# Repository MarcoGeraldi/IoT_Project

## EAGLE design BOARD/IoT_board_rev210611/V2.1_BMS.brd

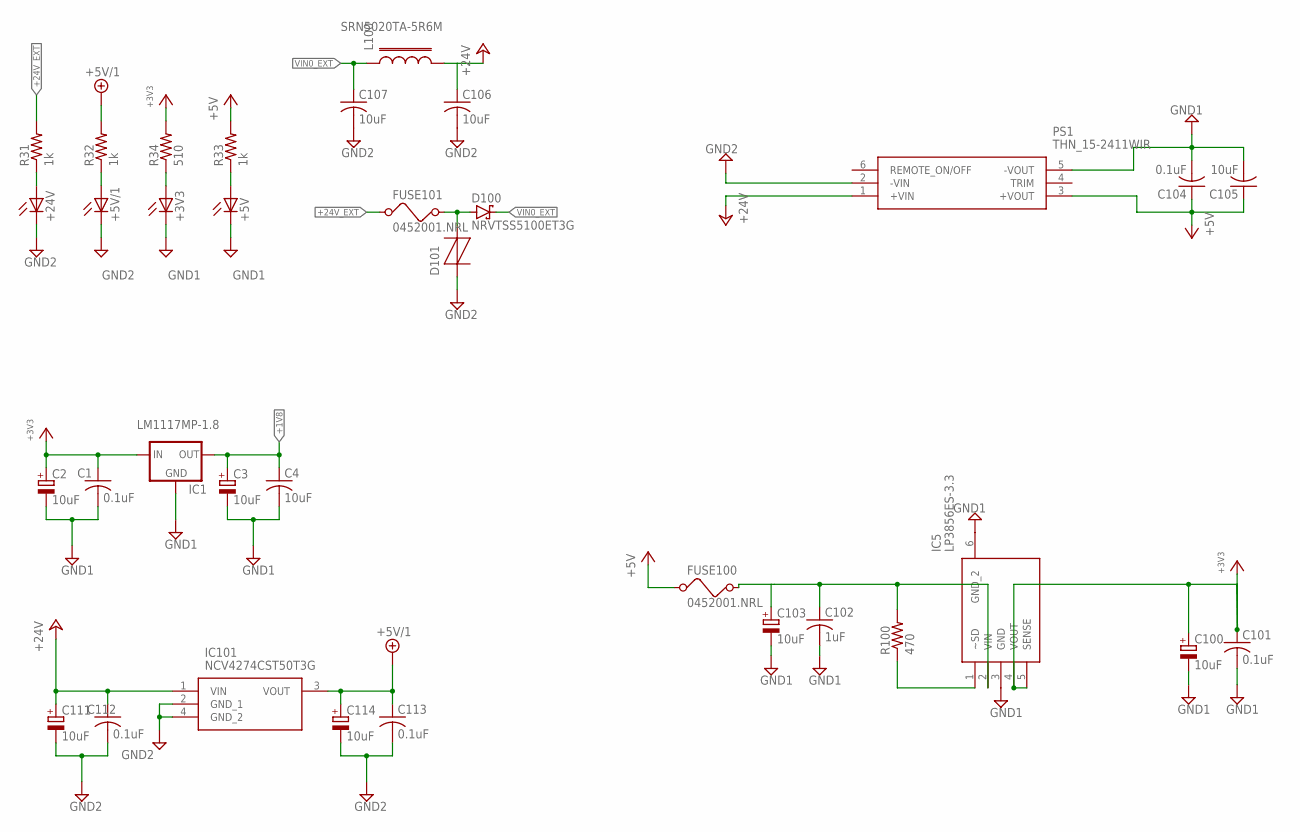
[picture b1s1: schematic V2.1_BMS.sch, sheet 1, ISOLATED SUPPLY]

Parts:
+3V3, +5V, +5V/1, +24V: LED0603; LED-0603
C1, C101, C104, C112, C113: 0.1uF; 0603_INCH:1
C2, C3, C100, C103, C111, C114: 10uF; CAPMP3528X210N
C4, C105, C106, C107: 10uF; 0603_INCH:1
C102: 1uF; 0603_INCH:1
D100: NRVTSS5100ET3G; LIBRARY_DIODES_FUSE_SMB-2
D101: P0300SCLRP; LIBRARY_DIODES_FUSE_SMB
FUSE100, FUSE101: 0452001.NRL; LIBRARY_DIODES_FUSE_452_454
IC1: LM1117MP-1.8; SOT223:1
IC5: LP3856ES-3.3; TO170P1435X465-6N
IC101: NCV4274CST50T3G; SOT223
L100: SRN5020TA-5R6M; LIBRARY_DIODES_FUSE_L_5X5
PS1: THN_15-2411WIR; THN152415WIR
R31, R32, R33: 1k; 0603_INCH
R34: 510; 0603_INCH
R100: 470; 0603_INCH

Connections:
+1V8: C3.1 (+), C4.1, IC1.2 (OUT), IC1.4 (OUT); also elsewhere on the board
+3V3: C1.1, C2.1 (+), C100.1 (+), C101.1, IC1.3 (IN), IC5.4 (VOUT), IC5.5 (SENSE), R34.2; also elsewhere on the board
+5V: C104.1, C105.1, FUSE100.P$1 (1), PS1.3 (+VOUT), R33.2; also elsewhere on the board
+5V/1: C113.1, C114.1 (+), IC101.3 (VOUT), R32.2; also elsewhere on the board
+24V: C106.1, C111.1 (+), C112.1, IC101.1 (VIN), L100.P$2 (2), PS1.1 (+VIN)
+24V_EXT: FUSE101.P$1 (1), R31.2; also elsewhere on the board
GND1: +3V3.C, +5V.C, C1.2, C2.2 (-), C3.2 (-), C4.2, C100.2 (-), C101.2, C102.2, C103.2 (-), C104.2, C105.2, IC1.1 (GND), IC5.3 (GND), IC5.6 (GND_2), PS1.5 (-VOUT); also elsewhere on the board
GND2: +5V/1.C, +24V.C, C106.2, C107.2, C111.2 (-), C112.2, C113.2, C114.2 (-), D101.2 (T), IC101.2 (GND_1), IC101.4 (GND_2), PS1.2 (-VIN); also elsewhere on the board
unnamed: C102.1, C103.1 (+), FUSE100.P$2 (2), IC5.2 (VIN), R100.2
unnamed: D100.A, D101.1 (R), FUSE101.P$2 (2)
unnamed: IC5.1 (~SD), R100.1
unnamed: +5V/1.A, R32.1
unnamed: +5V.A, R33.1
unnamed: +24V.A, R31.1
unnamed: +3V3.A, R34.1
VIN0_EXT: C107.1, D100.C, L100.P$1 (1)

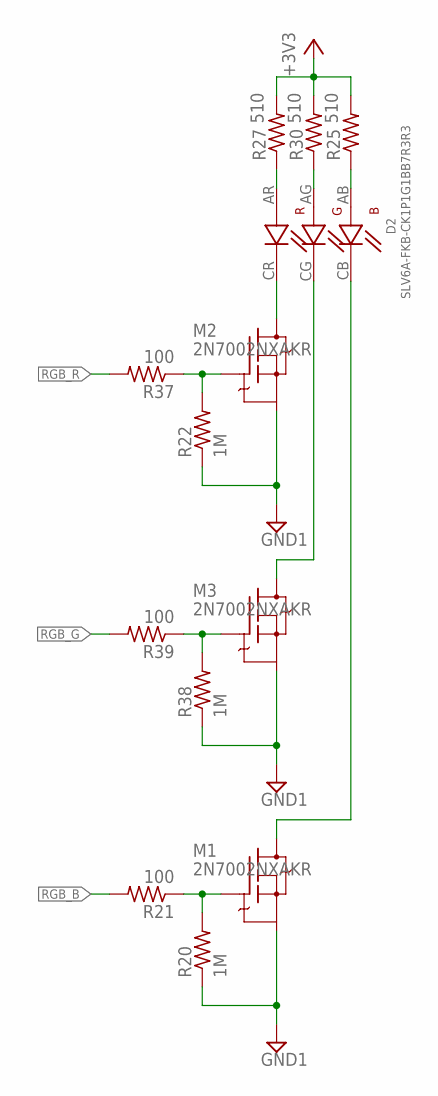
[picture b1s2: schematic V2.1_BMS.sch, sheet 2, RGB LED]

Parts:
D2: SLV6A-FKB-CK1P1G1BB7R3R3; PLCC-6-LED_PLCC-6-LED
M1, M2, M3: 2N7002NXAKR; BEOND_SOT23
R20, R22, R38: 1M; 0603_INCH
R21, R37, R39: 100; 0603_INCH
R25, R27, R30: 510; 0603_INCH

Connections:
+3V3: R25.2, R27.2, R30.2; also elsewhere on the board
GND1: M1.2 (S), M2.2 (S), M3.2 (S), R20.1, R22.1, R38.1; also elsewhere on the board
unnamed: D2.AR (RA), R27.1
unnamed: D2.AG (GA), R30.1
unnamed: D2.AB (BA), R25.1
unnamed: M3.1 (G), R38.2, R39.1
unnamed: D2.CG (GC), M3.3 (D)
unnamed: M1.1 (G), R20.2, R21.1
unnamed: D2.CB (BC), M1.3 (D)
unnamed: M2.1 (G), R22.2, R37.1
unnamed: D2.CR (RC), M2.3 (D)
RGB_B: R21.2; also elsewhere on the board
RGB_G: R39.2; also elsewhere on the board
RGB_R: R37.2; also elsewhere on the board

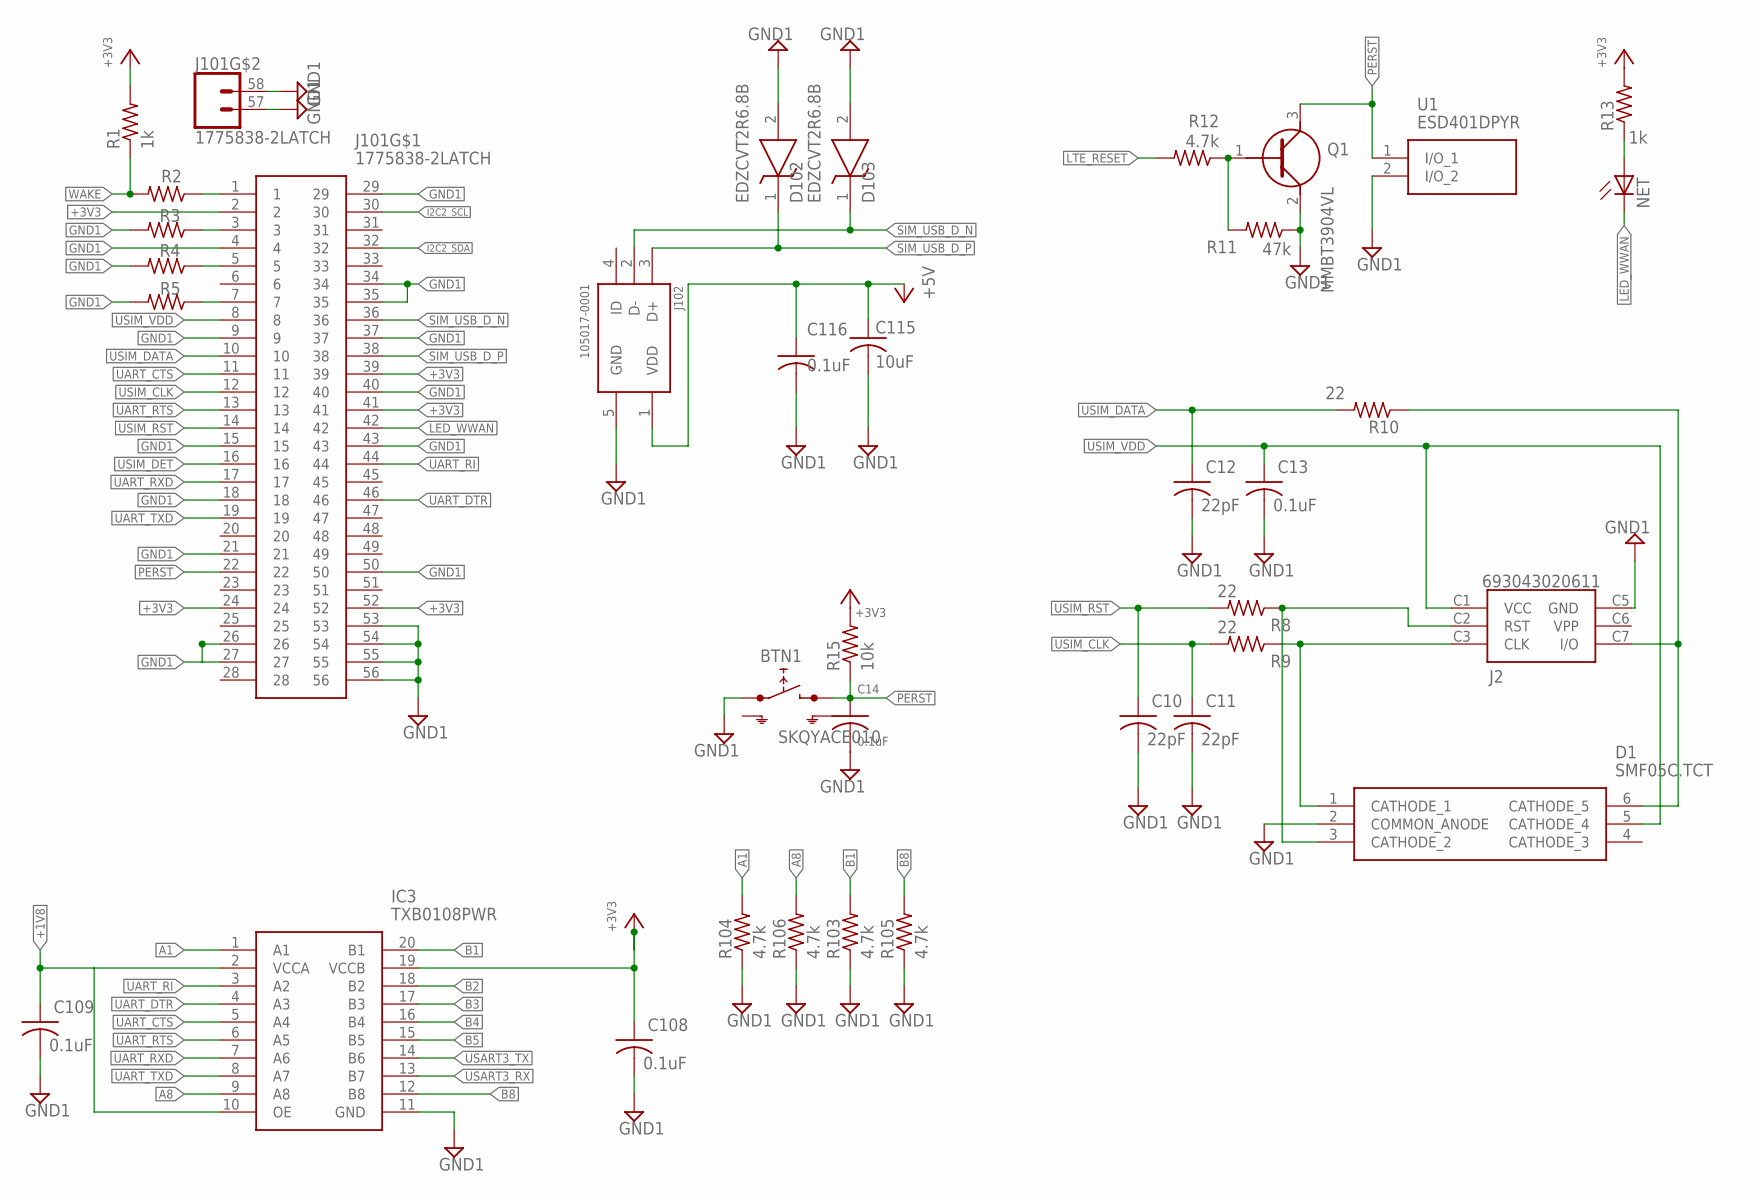
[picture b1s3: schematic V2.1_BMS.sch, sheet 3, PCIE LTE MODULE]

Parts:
BTN1: SKQYACE010; BOTON_LED_SKQYACE010
C10, C11, C12: 22pF; 0603_INCH:1
C13, C14, C108, C109, C116: 0.1uF; 0603_INCH:1
C115: 10uF; 0603_INCH:1
D1: SMF05C.TCT; SOT65P210X110-6N
D102, D103: EDZCVT2R6.8B; SODFL1608X70N
IC3: TXB0108PWR; SOP65P640X120-20N
J2: 693043020611
J101: 1775838-2LATCH; 17758382_LATCH
J102: 105017-0001; MOLEX_105017-0001
NET: LED0603; LED-0603
Q1: MMBT3904VL; SOT95P230X110-3N
R1, R13: 1k; 0603_INCH
R2, R3, R4, R5: 0; 0603_INCH
R8, R9, R10: 22; 0603_INCH
R11: 47k; 0603_INCH
R12, R103, R104, R105, R106: 4.7k; 0603_INCH
R15: 10k; 0603_INCH
U1: ESD401DPYR

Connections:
+1V8: C109.1, IC3.2 (VCCA), IC3.10 (OE); also elsewhere on the board
+3V3: C108.1, IC3.19 (VCCB), J101.2, J101.24, J101.39, J101.41, J101.52, R1.2, R13.2, R15.2; also elsewhere on the board
+5V: C115.1, C116.1, J102.1 (VDD); also elsewhere on the board
A1: IC3.1 (A1), R104.2
A8: IC3.9 (A8), R106.2
B1: IC3.20 (B1), R103.2
B2: IC3.18 (B2)
B3: IC3.17 (B3)
B4: IC3.16 (B4)
B5: IC3.15 (B5)
B8: IC3.12 (B8), R105.2
GND1: BTN1.1 (1.1), C10.2, C11.2, C12.2, C13.2, C14.2, C108.2, C109.2, C115.2, C116.2, D1.2 (COMMON_ANODE), D102.2 (A), D103.2 (A), IC3.11 (GND), J2.C5 (GND), J101.4, J101.9, J101.15, J101.18, J101.21, J101.26, J101.27, J101.29, J101.34, J101.35, J101.37, J101.40, J101.43, J101.50, J101.53, J101.54, J101.55, J101.56, J101.57 (1), J101.58 (2), J102.5 (GND), Q1.2 (E), R3.2, R4.2, R5.2, R11.1, R103.1, R104.1, R105.1, R106.1, U1.2 (I/O_2); also elsewhere on the board
I2C2_SCL: J101.30; also elsewhere on the board
I2C2_SDA: J101.32; also elsewhere on the board
LED_WWAN: J101.42, NET.C
LTE_RESET: R12.2
unnamed: J101.3, R3.1
unnamed: J101.5, R4.1
unnamed: Q1.1 (B), R11.2, R12.1
unnamed: NET.A, R13.1
unnamed: D1.3 (CATHODE_2), J2.C2 (RST), R8.1
unnamed: J101.7, R5.1
unnamed: J101.1, R2.1
PERST: BTN1.2 (2.1), C14.1, J101.22, Q1.3 (C), R15.1, U1.1 (I/O_1)
SIM_USB_D_N: D103.1 (K), J101.36, J102.2 (D-)
SIM_USB_D_P: D102.1 (K), J101.38, J102.3 (D+)
UART_CTS: IC3.5 (A4), J101.11
UART_DTR: IC3.4 (A3), J101.46
UART_RI: IC3.3 (A2), J101.44
UART_RTS: IC3.6 (A5), J101.13
UART_RXD: IC3.7 (A6), J101.17
UART_TXD: IC3.8 (A7), J101.19
USART3_RX: IC3.13 (B7); also elsewhere on the board
USART3_TX: IC3.14 (B6); also elsewhere on the board
USIM_CLK: C11.1, J101.12, R9.2
USIM_DATA: C12.1, J101.10, R10.2
USIM_DET: J101.16
USIM_RST: C10.1, J101.14, R8.2
USIM_VDD: C13.1, D1.5 (CATHODE_4), J2.C1 (VCC), J101.8
WAKE: R1.1, R2.2
_USIM_CLK: D1.1 (CATHODE_1), J2.C3 (CLK), R9.1
_USIM_DATA: D1.6 (CATHODE_5), J2.C7 (I/O), R10.1

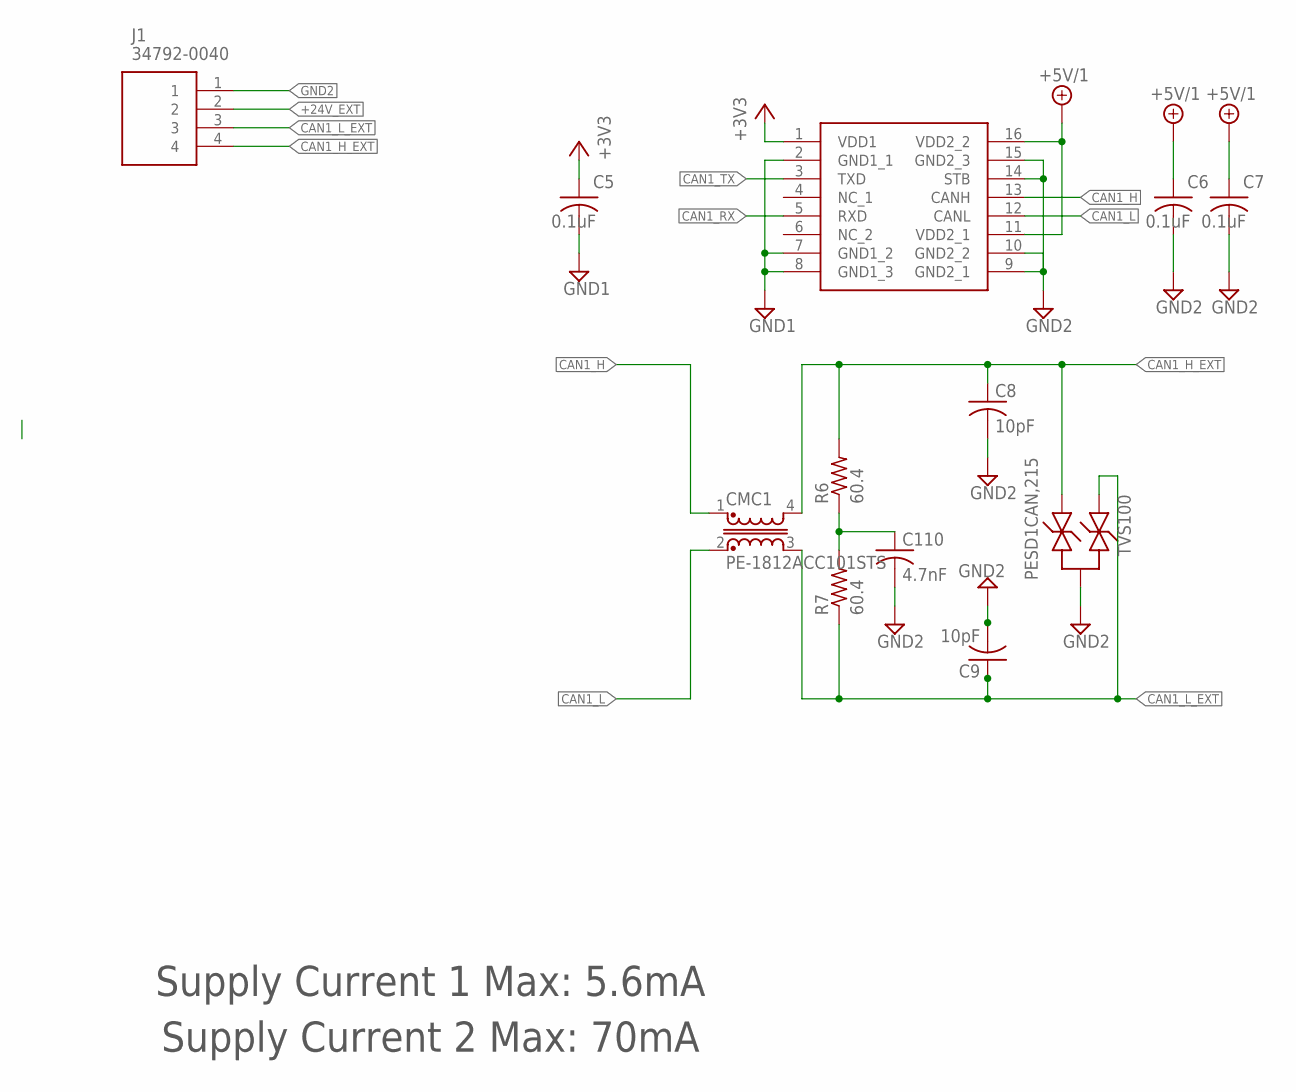
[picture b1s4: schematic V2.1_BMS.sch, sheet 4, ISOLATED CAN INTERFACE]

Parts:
C5, C6, C7: 0.1uF; 0603_INCH:1
C8, C9: 10pF; 0603_INCH:1
C110: 4.7nF; 0603_INCH:1
CMC1: PE-1812ACC101STS; BEOND_L_1812ACC
IC2: TJA1052IT/2Y; TJA1052IT_2Y_SOIC127P1032X265-16N
J1: 34792-0040; 347920040
R6, R7: 60.4; 0603_INCH
TVS100: PESD1CAN,215; BEOND_SOT23

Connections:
+3V3: C5.1, IC2.1 (VDD1); also elsewhere on the board
+5V/1: C6.1, C7.1, IC2.11 (VDD2_1), IC2.16 (VDD2_2); also elsewhere on the board
+24V_EXT: J1.2; also elsewhere on the board
CAN1_H: CMC1.1, IC2.13 (CANH)
CAN1_H_EXT: C8.1, CMC1.4, J1.4, R6.2, TVS100.2
CAN1_L: CMC1.2, IC2.12 (CANL)
CAN1_L_EXT: C9.1, CMC1.3, J1.3, R7.1, TVS100.1
CAN1_RX: IC2.5 (RXD); also elsewhere on the board
CAN1_TX: IC2.3 (TXD); also elsewhere on the board
GND1: C5.2, IC2.2 (GND1_1), IC2.7 (GND1_2), IC2.8 (GND1_3); also elsewhere on the board
GND2: C6.2, C7.2, C8.2, C9.2, C110.2, IC2.9 (GND2_1), IC2.10 (GND2_2), IC2.14 (STB), IC2.15 (GND2_3), J1.1, TVS100.3; also elsewhere on the board
unnamed: C110.1, R6.1, R7.2

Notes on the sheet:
Supply Current 2 Max: 70mA
Supply Current 1 Max: 5.6mA

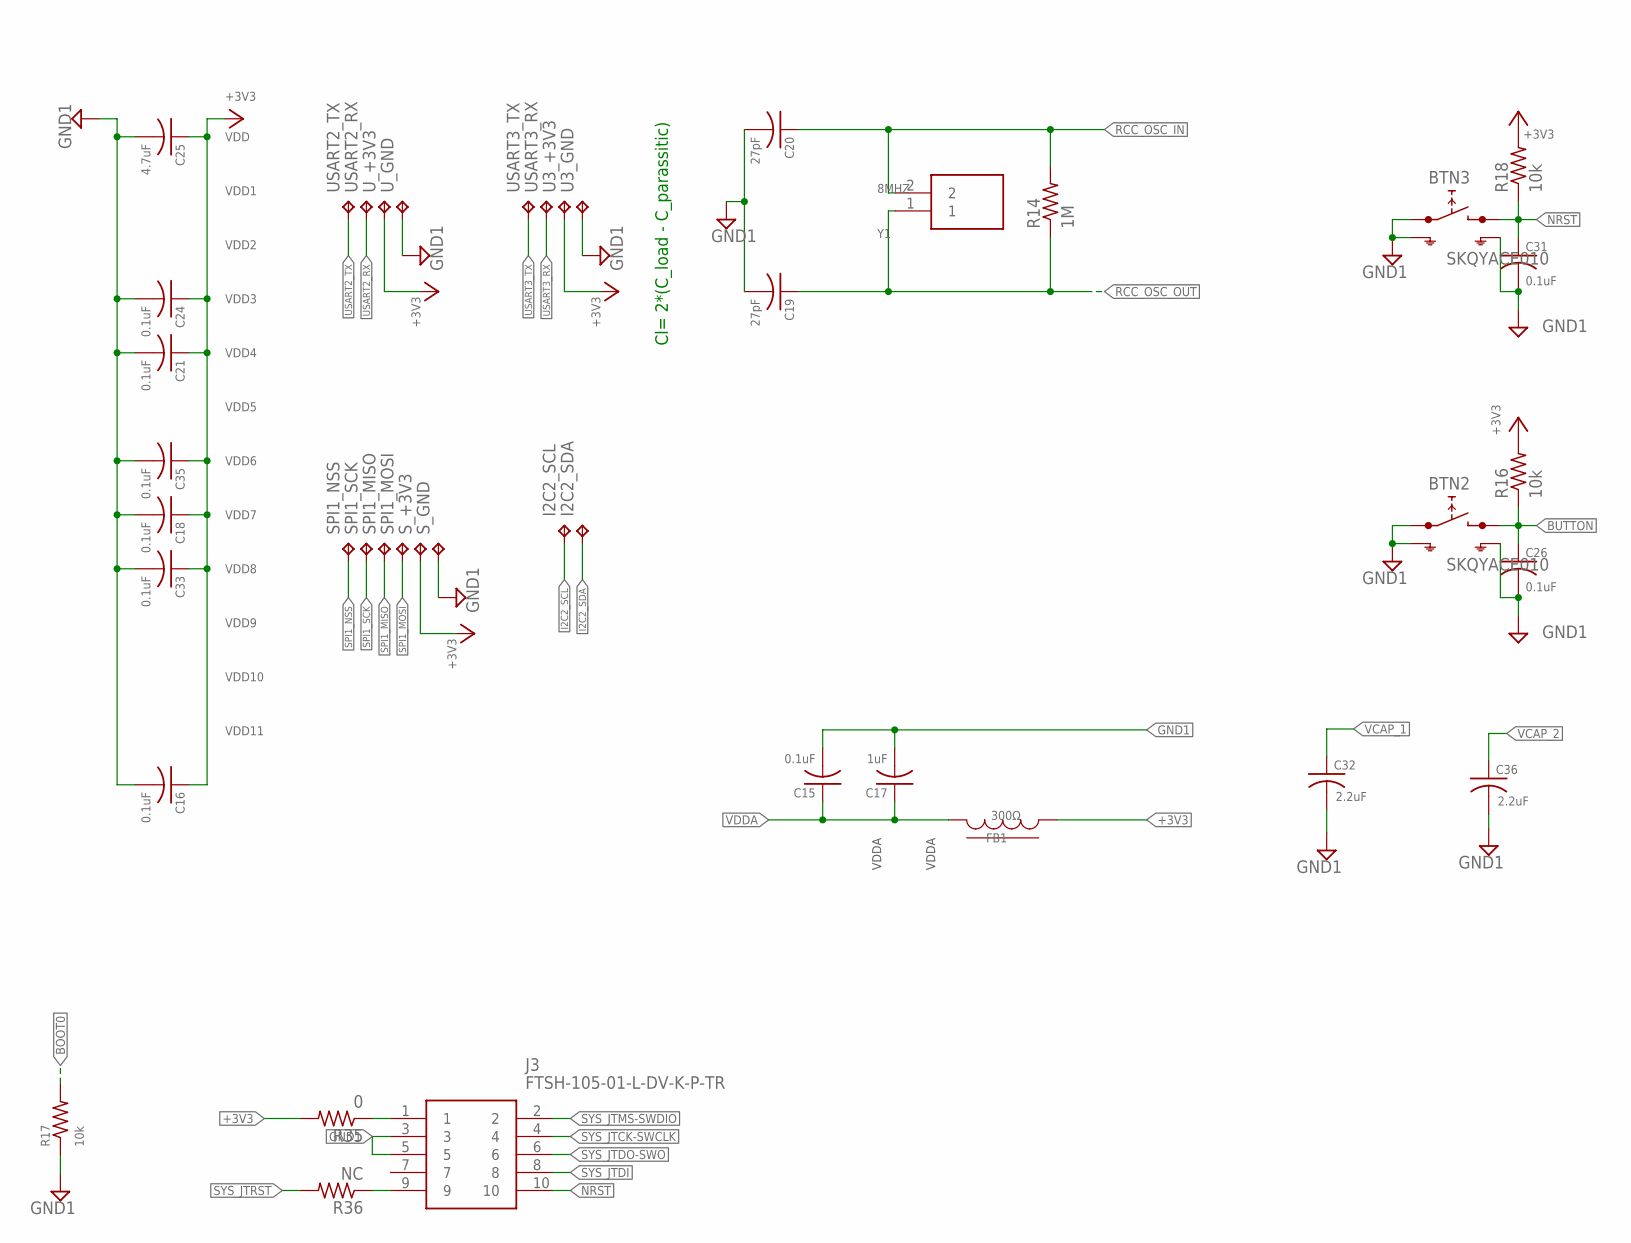
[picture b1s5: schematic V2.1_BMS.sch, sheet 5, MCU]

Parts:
BTN2, BTN3: SKQYACE010; BOTON_LED_SKQYACE010
C15, C16, C18, C21, C24, C33, C35: 0.1uF; 0603_INCH:1
C17: 1uF; 0603_INCH:1
C19, C20: 27pF; 0603_INCH
C25: 4.7uF; 0603_INCH:1
C26, C31: 0.1uF; 0603_INCH
C32, C36: 2.2uF; 0603_INCH:1
FB1: 300Ω; 0603_INCH
I2C2_SCL, I2C2_SDA: TPTP09R; TP09R
J3: FTSH-105-01-L-DV-K-P-TR; FTSH10501LDVKPTR
R14: 1M; 0603_INCH
R16, R17, R18: 10k; 0603_INCH
R35: 0; 0603_INCH
R36: NC; 0603_INCH
SPI1_MISO, SPI1_MOSI, SPI1_NSS, SPI1_SCK: TPTP09R; TP09R
S_+3V3: TPTP09R; TP09R
S_GND: TPTP09SQ; TP09SQ
U3_+3V3: TPTP09R; TP09R
U3_GND: TPTP09SQ; TP09SQ
USART2_RX, USART2_TX, USART3_RX, USART3_TX: TPTP09R; TP09R
U_+3V3: TPTP09R; TP09R
U_GND: TPTP09SQ; TP09SQ
Y1: 8MHZ; RESC3226X100N

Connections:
+3V1: U3_+3V3.TP
+3V3: C16.1, C18.1, C21.1, C24.1, C25.1, C33.1, C35.1, FB1.1, R16.2, R18.2, R35.2, S_+3V3.TP, U_+3V3.TP; also elsewhere on the board
BOOT0: R17.2; also elsewhere on the board
BUTTON: BTN2.2 (2.1), C26.1, R16.1; also elsewhere on the board
GND1: BTN2.1 (1.1), BTN2.GND1 (SH), BTN2.GND2 (SH1), BTN3.1 (1.1), BTN3.GND1 (SH), BTN3.GND2 (SH1), C15.2, C16.2, C17.2, C18.2, C19.2, C20.2, C21.2, C24.2, C25.2, C26.2, C31.2, C32.2, C33.2, C35.2, C36.2, J3.3, J3.5, R17.1, S_GND.TP, U_GND.TP; also elsewhere on the board
GND3: U3_GND.TP
I2C2_SCL: I2C2_SCL.TP; also elsewhere on the board
I2C2_SDA: I2C2_SDA.TP; also elsewhere on the board
unnamed: J3.1, R35.1
unnamed: J3.9, R36.1
NRST: BTN3.2 (2.1), C31.1, J3.10, R18.1; also elsewhere on the board
RCC_OSC_IN: C20.1, R14.2, Y1.2; also elsewhere on the board
RCC_OSC_OUT: C19.1, R14.1, Y1.1; also elsewhere on the board
SPI1_MISO: SPI1_MISO.TP; also elsewhere on the board
SPI1_MOSI: SPI1_MOSI.TP; also elsewhere on the board
SPI1_NSS: SPI1_NSS.TP; also elsewhere on the board
SPI1_SCK: SPI1_SCK.TP; also elsewhere on the board
SYS_JTCK-SWCLK: J3.4; also elsewhere on the board
SYS_JTDI: J3.8; also elsewhere on the board
SYS_JTDO-SWO: J3.6; also elsewhere on the board
SYS_JTMS-SWDIO: J3.2; also elsewhere on the board
SYS_JTRST: R36.2; also elsewhere on the board
USART2_RX: USART2_RX.TP; also elsewhere on the board
USART2_TX: USART2_TX.TP; also elsewhere on the board
USART3_RX: USART3_RX.TP; also elsewhere on the board
USART3_TX: USART3_TX.TP; also elsewhere on the board
VCAP_1: C32.1; also elsewhere on the board
VCAP_2: C36.1; also elsewhere on the board
VDDA: C15.1, C17.1, FB1.2; also elsewhere on the board

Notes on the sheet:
VDD1
VDD2
VDD3
VDD4
VDD
VDD5
VDD6
VDD7
VDD8
VDD9
VDD10
VDD11
VDDA
Cl= 2*(C_load - C_parassitic)

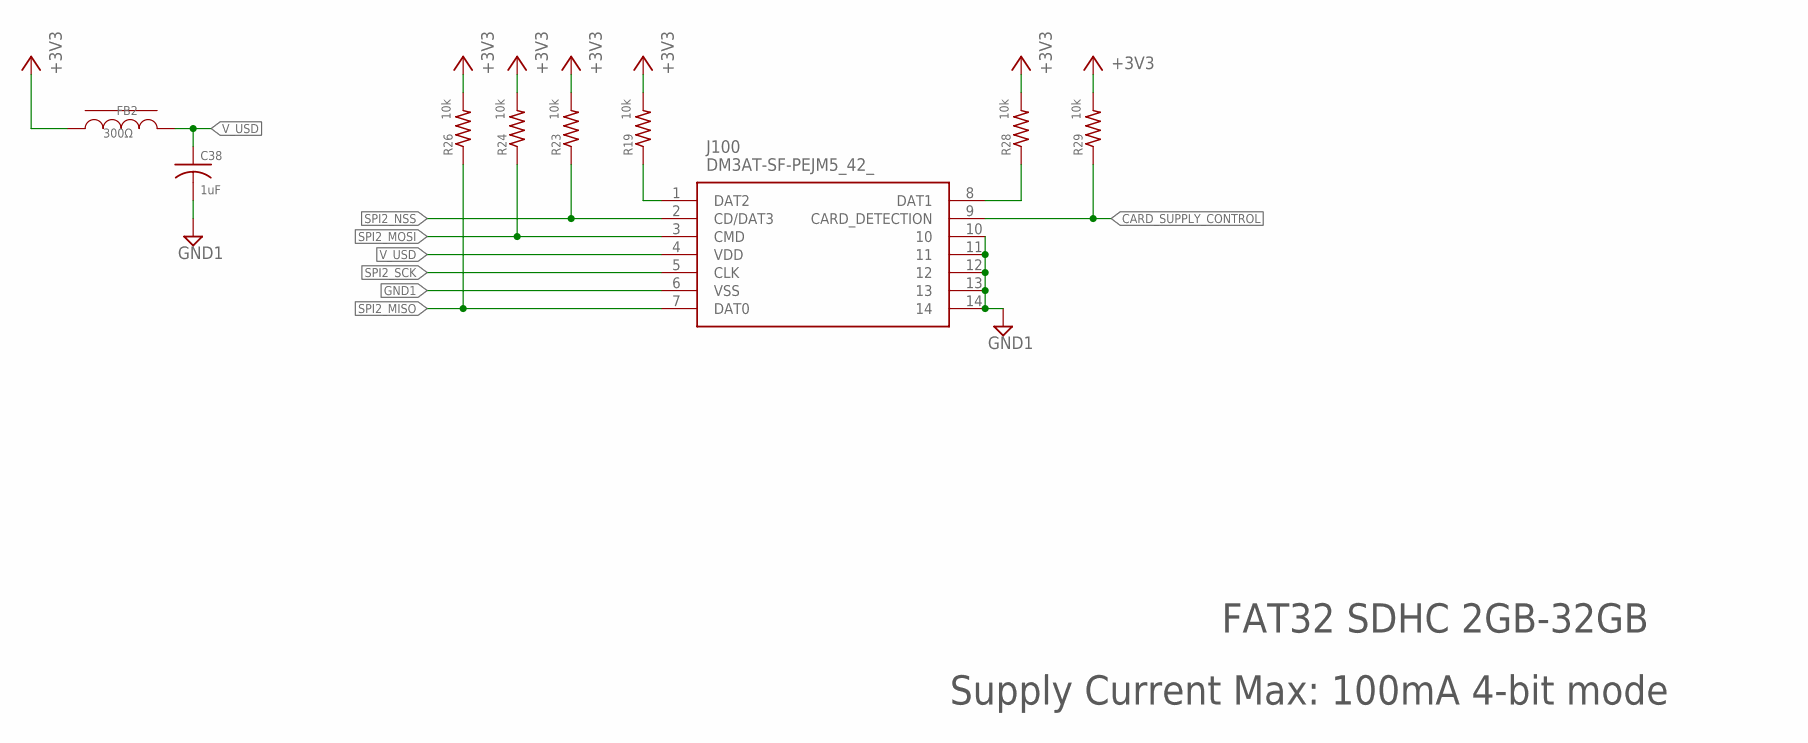
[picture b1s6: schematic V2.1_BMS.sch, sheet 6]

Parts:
C38: 1uF; 0603_INCH
FB2: 300Ω; 0603_INCH
J100: DM3AT-SF-PEJM5_42_; DM3ATSFPEJM542
R19, R23, R24, R26, R28, R29: 10k; 0603_INCH

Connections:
+3V3: FB2.1, R19.2, R23.2, R24.2, R26.2, R28.2, R29.2; also elsewhere on the board
CARD_SUPPLY_CONTROL: J100.9 (CARD_DETECTION), R29.1; also elsewhere on the board
GND1: C38.2, J100.6 (VSS), J100.10, J100.11, J100.12, J100.13, J100.14; also elsewhere on the board
unnamed: J100.1 (DAT2), R19.1
unnamed: J100.8 (DAT1), R28.1
SPI2_MISO: J100.7 (DAT0), R26.1; also elsewhere on the board
SPI2_MOSI: J100.3 (CMD), R24.1; also elsewhere on the board
SPI2_NSS: J100.2 (CD/DAT3), R23.1; also elsewhere on the board
SPI2_SCK: J100.5 (CLK); also elsewhere on the board
V_USD: C38.1, FB2.2, J100.4 (VDD)

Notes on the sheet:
Supply Current Max: 100mA 4-bit mode
FAT32 SDHC 2GB-32GB

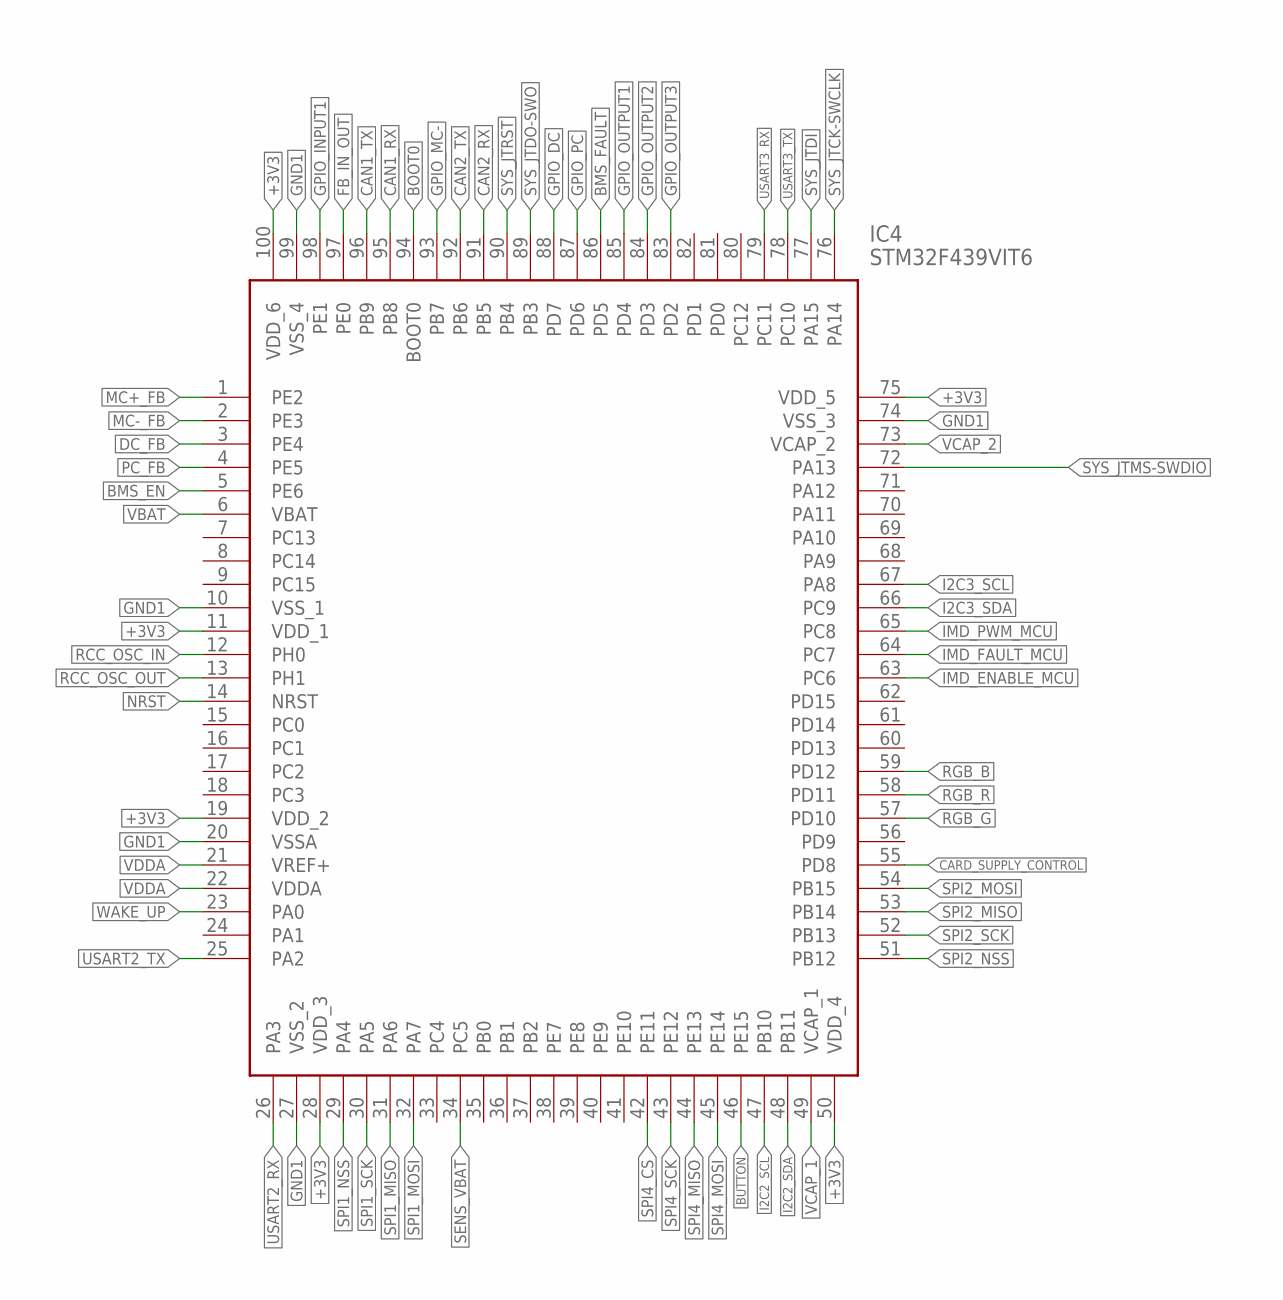
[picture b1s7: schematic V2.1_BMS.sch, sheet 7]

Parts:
IC4: STM32F439VIT6; QFP50P1600X1600X160-100N

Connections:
+3V3: IC4.11 (VDD_1), IC4.19 (VDD_2), IC4.28 (VDD_3), IC4.50 (VDD_4), IC4.75 (VDD_5), IC4.100 (VDD_6); also elsewhere on the board
BMS_EN: IC4.5 (PE6)
BMS_FAULT: IC4.86 (PD5)
BOOT0: IC4.94 (BOOT0); also elsewhere on the board
BUTTON: IC4.46 (PE15); also elsewhere on the board
CAN1_RX: IC4.95 (PB8); also elsewhere on the board
CAN1_TX: IC4.96 (PB9); also elsewhere on the board
CAN2_RX: IC4.91 (PB5)
CAN2_TX: IC4.92 (PB6)
CARD_SUPPLY_CONTROL: IC4.55 (PD8); also elsewhere on the board
DC_FB: IC4.3 (PE4)
FB_IN_OUT: IC4.97 (PE0)
GND1: IC4.10 (VSS_1), IC4.20 (VSSA), IC4.27 (VSS_2), IC4.74 (VSS_3), IC4.99 (VSS_4); also elsewhere on the board
GPIO_DC: IC4.88 (PD7)
GPIO_INPUT1: IC4.98 (PE1)
GPIO_MC-: IC4.93 (PB7)
GPIO_OUTPUT1: IC4.85 (PD4)
GPIO_OUTPUT2: IC4.84 (PD3)
GPIO_OUTPUT3: IC4.83 (PD2)
GPIO_PC: IC4.87 (PD6)
I2C2_SCL: IC4.47 (PB10); also elsewhere on the board
I2C2_SDA: IC4.48 (PB11); also elsewhere on the board
I2C3_SCL: IC4.67 (PA8)
I2C3_SDA: IC4.66 (PC9)
IMD_ENABLE_MCU: IC4.63 (PC6)
IMD_FAULT_MCU: IC4.64 (PC7)
IMD_PWM_MCU: IC4.65 (PC8)
MC+_FB: IC4.1 (PE2)
MC-_FB: IC4.2 (PE3)
NRST: IC4.14 (NRST); also elsewhere on the board
PC_FB: IC4.4 (PE5)
RCC_OSC_IN: IC4.12 (PH0); also elsewhere on the board
RCC_OSC_OUT: IC4.13 (PH1); also elsewhere on the board
RGB_B: IC4.59 (PD12); also elsewhere on the board
RGB_G: IC4.57 (PD10); also elsewhere on the board
RGB_R: IC4.58 (PD11); also elsewhere on the board
SENS_VBAT: IC4.34 (PC5)
SPI1_MISO: IC4.31 (PA6); also elsewhere on the board
SPI1_MOSI: IC4.32 (PA7); also elsewhere on the board
SPI1_NSS: IC4.29 (PA4); also elsewhere on the board
SPI1_SCK: IC4.30 (PA5); also elsewhere on the board
SPI2_MISO: IC4.53 (PB14); also elsewhere on the board
SPI2_MOSI: IC4.54 (PB15); also elsewhere on the board
SPI2_NSS: IC4.51 (PB12); also elsewhere on the board
SPI2_SCK: IC4.52 (PB13); also elsewhere on the board
SPI4_CS: IC4.42 (PE11)
SPI4_MISO: IC4.44 (PE13)
SPI4_MOSI: IC4.45 (PE14)
SPI4_SCK: IC4.43 (PE12)
SYS_JTCK-SWCLK: IC4.76 (PA14); also elsewhere on the board
SYS_JTDI: IC4.77 (PA15); also elsewhere on the board
SYS_JTDO-SWO: IC4.89 (PB3); also elsewhere on the board
SYS_JTMS-SWDIO: IC4.72 (PA13); also elsewhere on the board
SYS_JTRST: IC4.90 (PB4); also elsewhere on the board
USART2_RX: IC4.26 (PA3); also elsewhere on the board
USART2_TX: IC4.25 (PA2); also elsewhere on the board
USART3_RX: IC4.79 (PC11); also elsewhere on the board
USART3_TX: IC4.78 (PC10); also elsewhere on the board
VBAT: IC4.6 (VBAT)
VCAP_1: IC4.49 (VCAP_1); also elsewhere on the board
VCAP_2: IC4.73 (VCAP_2); also elsewhere on the board
VDDA: IC4.21 (VREF+), IC4.22 (VDDA); also elsewhere on the board
WAKE_UP: IC4.23 (PA0)

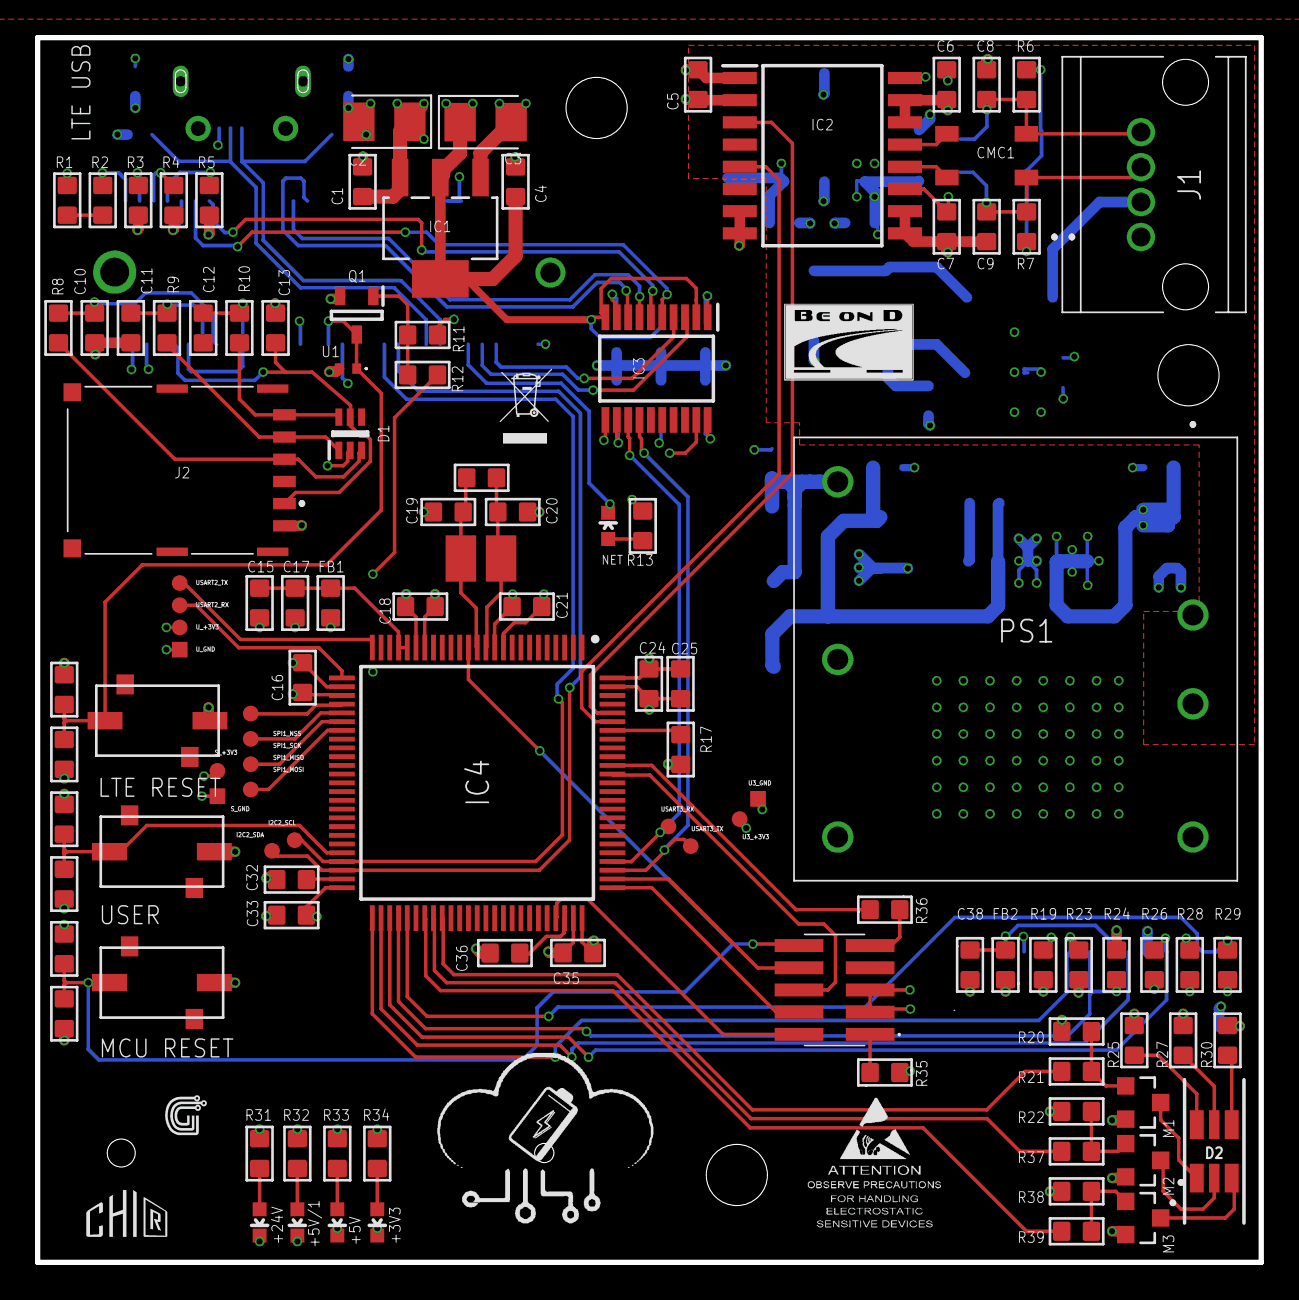
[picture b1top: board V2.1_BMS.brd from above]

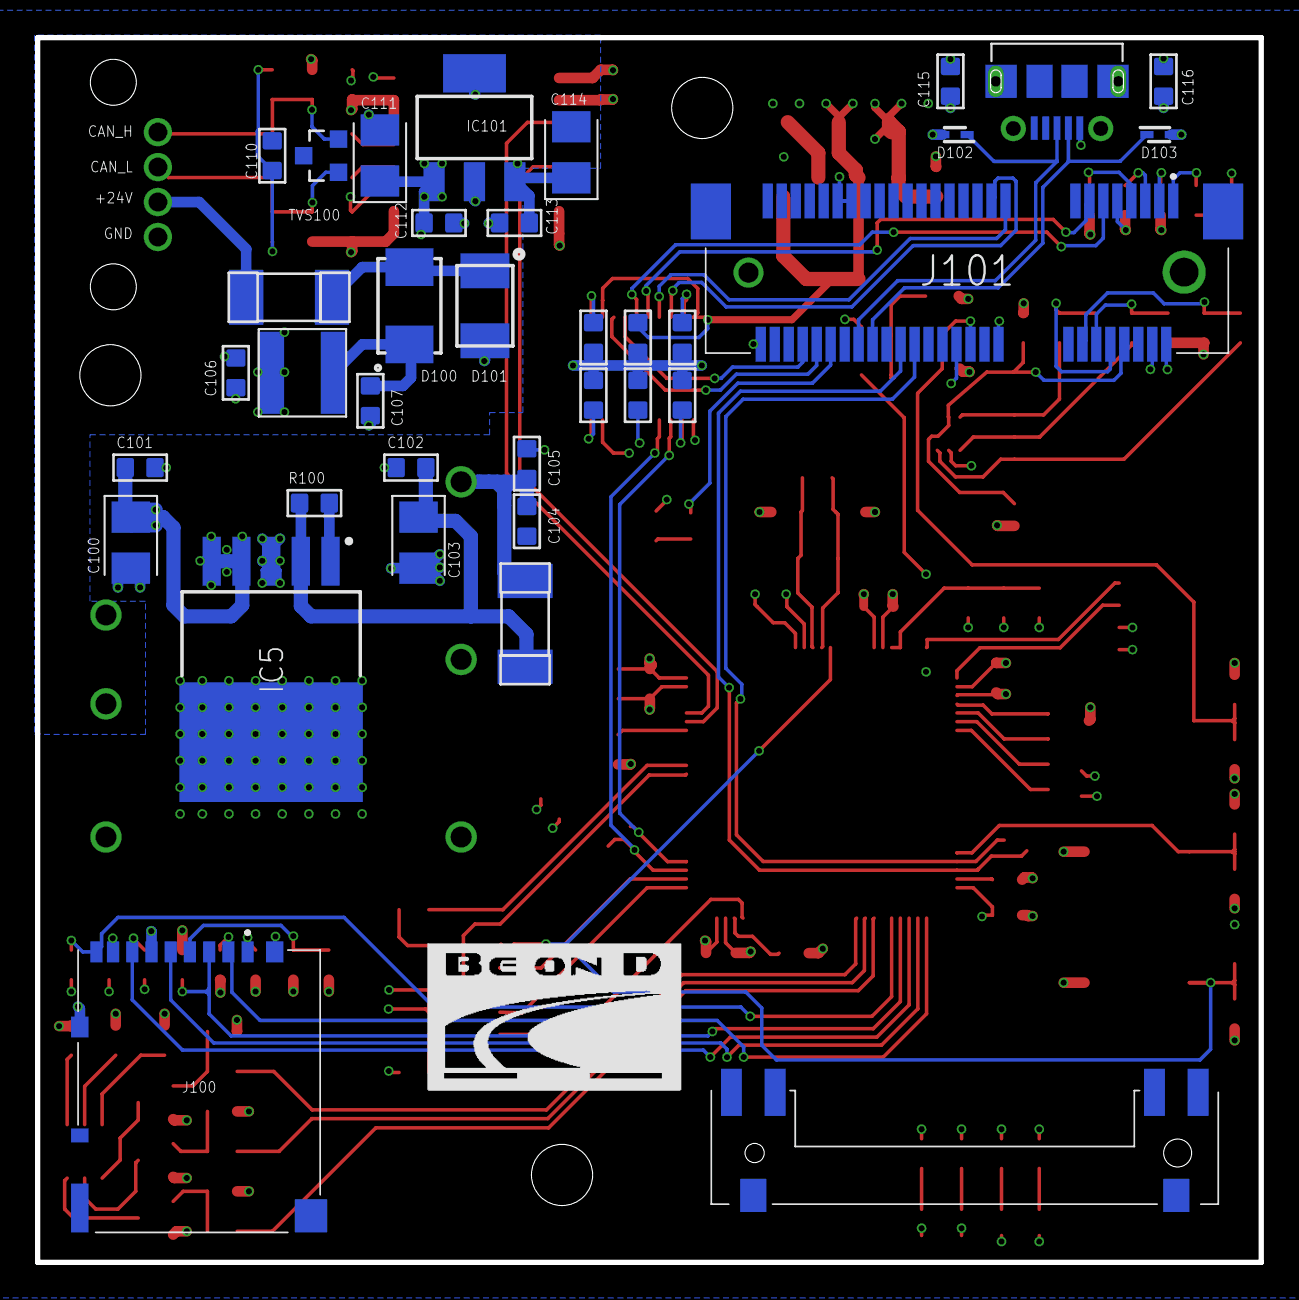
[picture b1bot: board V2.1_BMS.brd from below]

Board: 4 copper layers, 70.0 x 70.1 mm, 147 parts (35 on the bottom side), 96 nets.

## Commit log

2021-06-11 make rep
    Initial Rep commit
2021-06-15 SIM7800e DOCs
    Documentation of SIM7800e automotive module
2021-06-15 Create IoT_FW_STM32F429_rev210615.rar
    Publish on AWS working
2022-02-09 Create IoT_Board_stateMachine_211012.rar
    Backup of firmware with State machine
